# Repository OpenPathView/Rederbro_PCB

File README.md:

# Rederbro_PCB
All electronic parts related to rederbro (Open Path View, backpack).

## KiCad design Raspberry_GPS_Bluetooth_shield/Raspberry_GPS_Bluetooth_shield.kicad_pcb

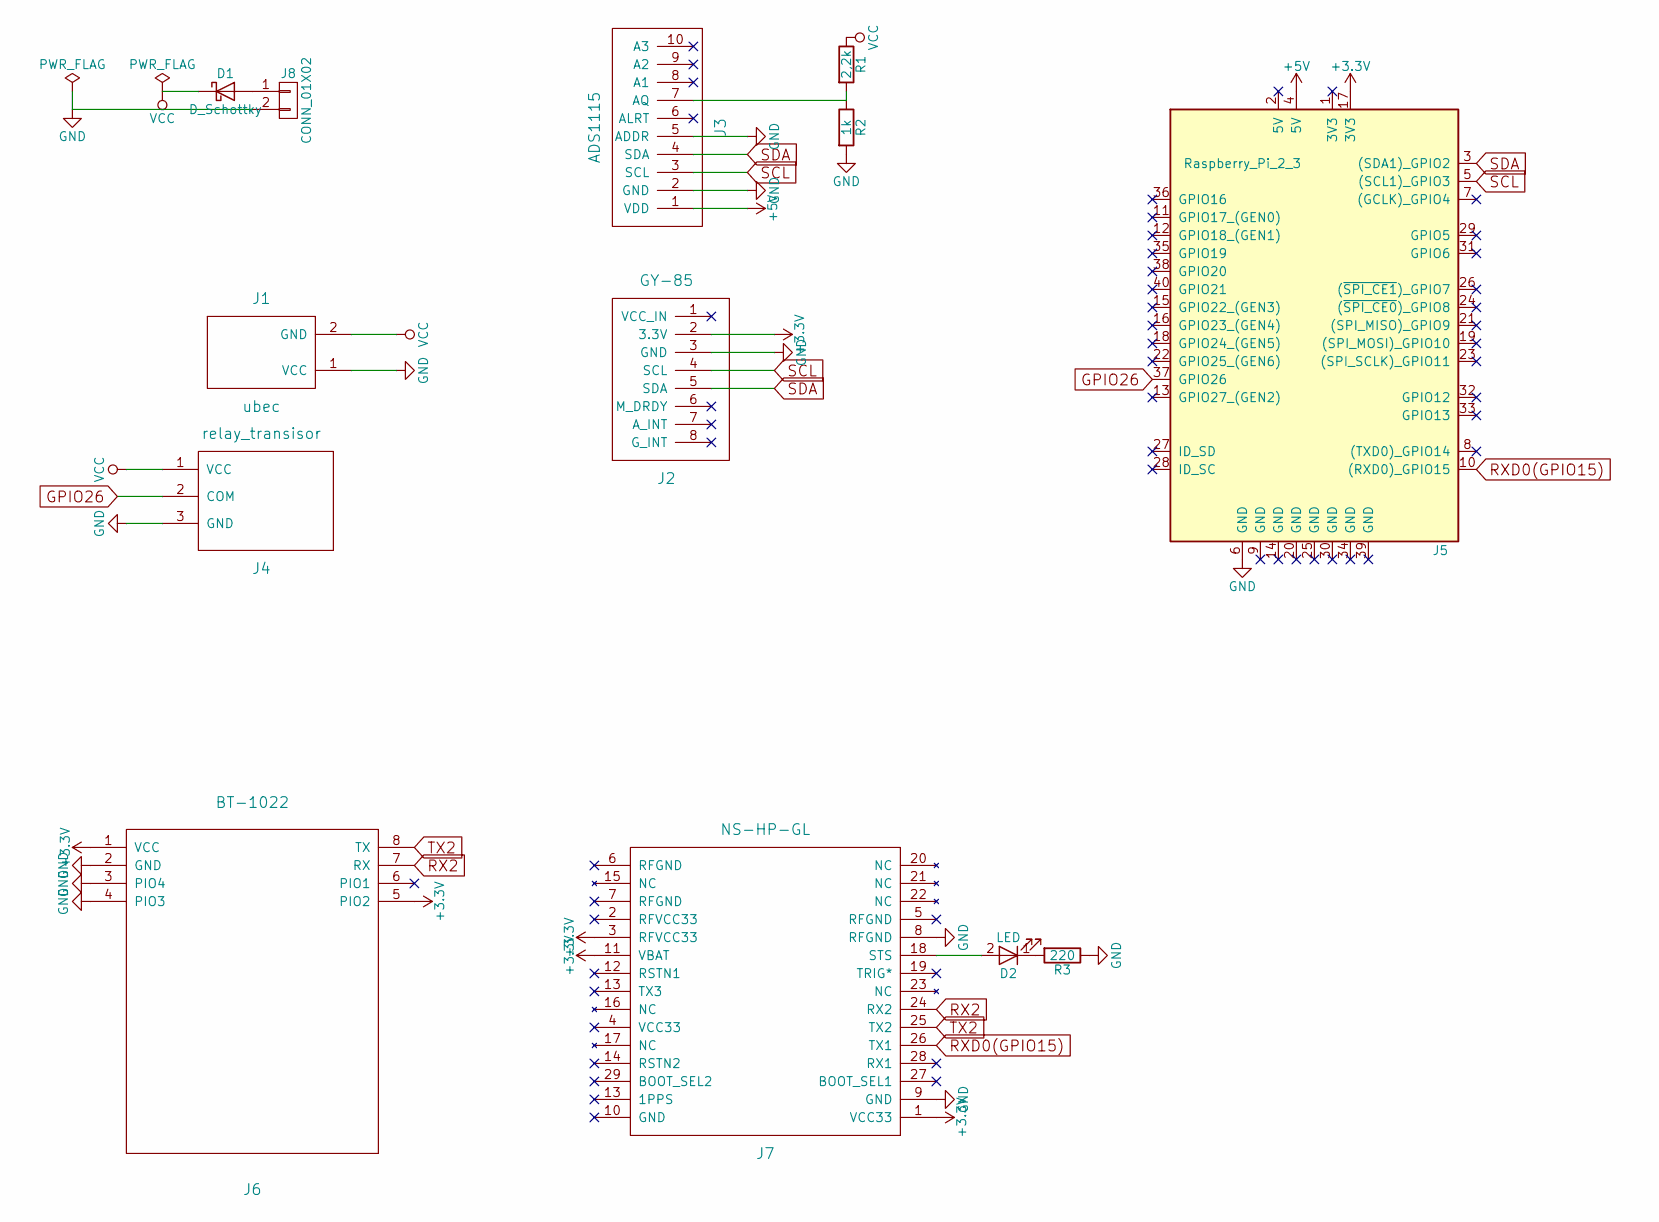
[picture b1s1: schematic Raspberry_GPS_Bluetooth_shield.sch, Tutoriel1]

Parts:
D1: D_Schottky; 1N5820
D2: LED; LED_0603
J1: ubec; PhoenixContact_MCV-G_02x3.50mm_Vertical
J2: GY-85; Pin_Header_Straight_1x08_Pitch2.54mm
J3: ADS1115; Pin_Header_Straight_1x10_Pitch2.54mm
J4: relay_transisor; PhoenixContact_MCV-G_03x5.08mm_Vertical
J5: Raspberry_Pi_2_3; Pin_Header_Straight_2x20_Pitch2.54mm
J6: BT-1022; BT_NAVSPARK
J7: NS-HP-GL
J8: CONN_01X02; PhoenixContact_MCV-G_02x3.50mm_Vertical
R1: 2,2k; R_0805_HandSoldering
R2: 1k; R_0805_HandSoldering
R3: 220; R_0805_HandSoldering

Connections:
+3V3: J2.2 (3.3V), J5.17 (3V3), J6.1 (VCC), J6.5 (PIO2), J7.1 (VCC33), J7.3 (RFVCC33), J7.11 (VBAT)
+5V: J3.1 (VDD), J5.4 (5V)
GND: J1.1 (VCC), J2.3 (GND), J3.2 (GND), J3.5 (ADDR), J4.3 (GND), J5.6 (GND), J6.2 (GND), J6.3 (PIO4), J6.4 (PIO3), J7.8 (RFGND), J7.9 (GND), J8.2, R2.2, R3.1
GPIO26: J4.2 (COM), J5.37 (GPIO26)
unnamed: D1.2 (A), J8.1
unnamed: D2.1 (K), R3.2
unnamed: D2.2 (A), J7.18 (STS)
unnamed: J3.7 (AQ), R1.2, R2.1
RX2: J6.7 (RX), J7.24 (RX2)
RXD0(GPIO15): J5.10 ((RXD0)_GPIO15), J7.26 (TX1)
SCL: J2.4 (SCL), J3.3 (SCL), J5.5 ((SCL1)_GPIO3)
SDA: J2.5 (SDA), J3.4 (SDA), J5.3 ((SDA1)_GPIO2)
TX2: J6.8 (TX), J7.25 (TX2)
VCC: D1.1 (K), J1.2 (GND), J4.1 (VCC), R1.1

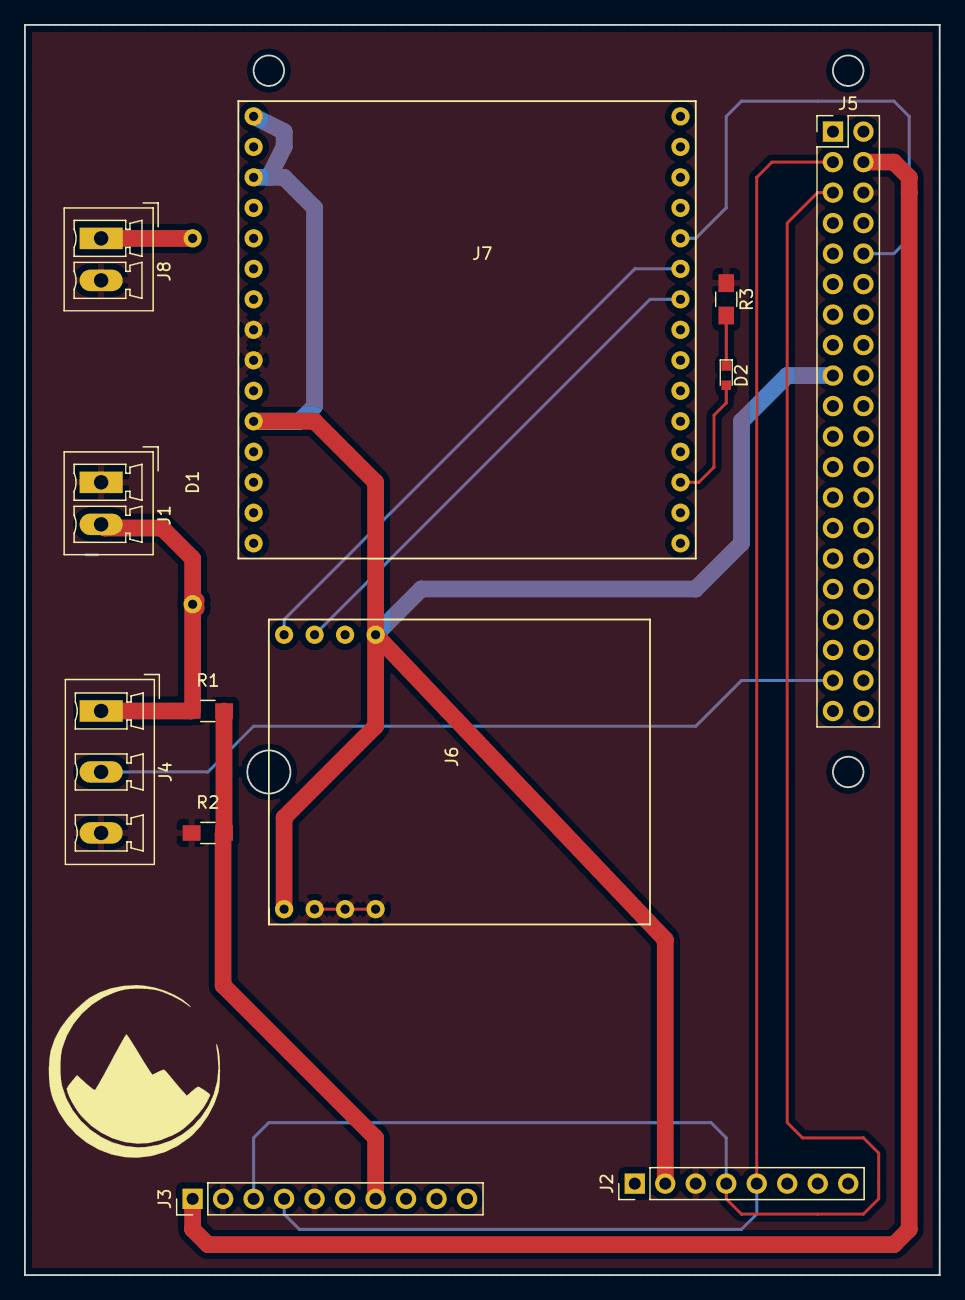
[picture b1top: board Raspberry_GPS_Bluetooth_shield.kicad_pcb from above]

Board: 2 copper layers, 76.2 x 104.1 mm, 13 parts (0 on the bottom side), 14 nets.

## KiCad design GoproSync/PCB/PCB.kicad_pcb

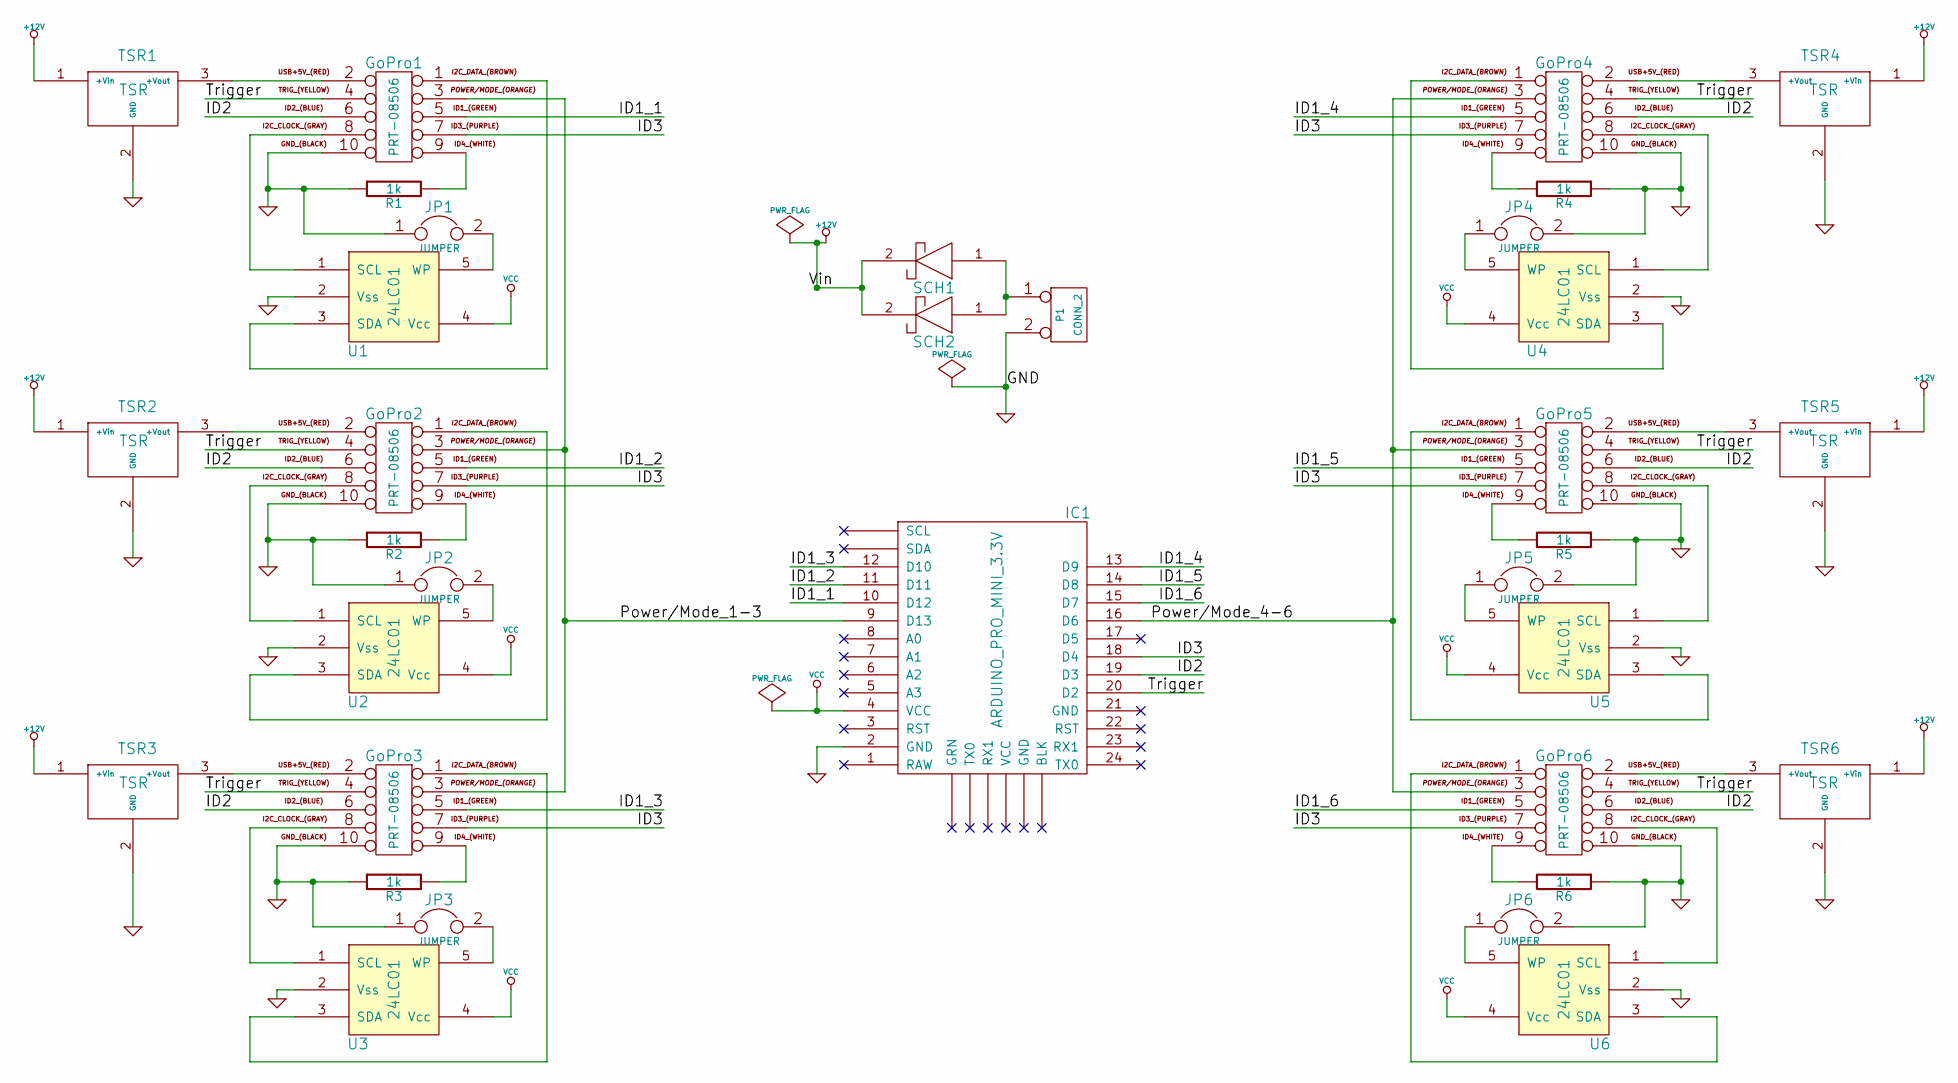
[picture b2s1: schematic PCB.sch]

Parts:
GoPro1, GoPro2, GoPro3, GoPro4, GoPro5, GoPro6: PRT-08506
IC1: ARDUINO_PRO_MINI_3.3V
JP1, JP2, JP3, JP4, JP5, JP6: JUMPER
P1: CONN_2
R1, R2, R3, R4, R5, R6: 1k
SCH1, SCH2: SCHOTTKY
TSR1, TSR2, TSR3, TSR4, TSR5, TSR6: TSR
U1, U2, U3, U4, U5, U6: 24LC01

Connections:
+12V: SCH1.2 (Cathode), SCH2.2 (Cathode), TSR1.1 (+Vin), TSR2.1 (+Vin), TSR3.1 (+Vin), TSR4.1 (+Vin), TSR5.1 (+Vin), TSR6.1 (+Vin)
/ID1_1: GoPro1.5, IC1.10 (D12)
/ID1_2: GoPro2.5, IC1.11 (D11)
/ID1_3: GoPro3.5, IC1.12 (D10)
/ID1_4: GoPro4.5, IC1.13 (D9)
/ID1_5: GoPro5.5, IC1.14 (D8)
/ID1_6: GoPro6.5, IC1.15 (D7)
/ID2: GoPro1.6, GoPro2.6, GoPro3.6, GoPro4.6, GoPro5.6, GoPro6.6, IC1.19 (D3)
/ID3: GoPro1.7, GoPro2.7, GoPro3.7, GoPro4.7, GoPro5.7, GoPro6.7, IC1.18 (D4)
/Power/Mode_1-3: GoPro1.3, GoPro2.3, GoPro3.3, IC1.9 (D13)
/Power/Mode_4-6: GoPro4.3, GoPro5.3, GoPro6.3, IC1.16 (D6)
/Trigger: GoPro1.4, GoPro2.4, GoPro3.4, GoPro4.4, GoPro5.4, GoPro6.4, IC1.20 (D2)
GND: GoPro1.10, GoPro2.10, GoPro3.10, GoPro4.10, GoPro5.10, GoPro6.10, IC1.2 (GND), JP1.1, JP2.1, JP3.1, JP4.2, JP5.2, JP6.2, P1.2 (PM), R1.1, R2.1, R3.1, R4.1, R5.1, R6.1, TSR1.2 (GND), TSR2.2 (GND), TSR3.2 (GND), TSR4.2 (GND), TSR5.2 (GND), TSR6.2 (GND), U1.2 (Vss), U2.2 (Vss), U3.2 (Vss), U4.2 (Vss), U5.2 (Vss), U6.2 (Vss)
unnamed: GoPro1.9, R1.2
unnamed: GoPro3.2, TSR3.3 (+Vout)
unnamed: GoPro3.9, R3.2
unnamed: GoPro6.9, R6.2
unnamed: GoPro6.1, U6.3 (SDA)
unnamed: GoPro6.2, TSR6.3 (+Vout)
unnamed: GoPro4.9, R4.2
unnamed: GoPro2.9, R2.2
unnamed: GoPro4.1, U4.3 (SDA)
unnamed: GoPro2.2, TSR2.3 (+Vout)
unnamed: GoPro2.8, U2.1 (SCL)
unnamed: GoPro1.2, TSR1.3 (+Vout)
unnamed: JP4.1, U4.5 (WP)
unnamed: JP1.2, U1.5 (WP)
unnamed: JP6.1, U6.5 (WP)
unnamed: GoPro6.8, U6.1 (SCL)
unnamed: JP5.1, U5.5 (WP)
unnamed: GoPro5.1, U5.3 (SDA)
unnamed: GoPro4.2, TSR4.3 (+Vout)
unnamed: GoPro4.8, U4.1 (SCL)
unnamed: GoPro5.8, U5.1 (SCL)
unnamed: GoPro5.2, TSR5.3 (+Vout)
unnamed: GoPro5.9, R5.2
unnamed: JP3.2, U3.5 (WP)
unnamed: JP2.2, U2.5 (WP)
unnamed: GoPro1.1, U1.3 (SDA)
unnamed: GoPro1.8, U1.1 (SCL)
unnamed: GoPro2.1, U2.3 (SDA)
unnamed: GoPro3.8, U3.1 (SCL)
unnamed: GoPro3.1, U3.3 (SDA)
unnamed: P1.1, SCH1.1 (Anode), SCH2.1 (Anode)
VCC: IC1.4 (VCC), U1.4 (Vcc), U2.4 (Vcc), U3.4 (Vcc), U4.4 (Vcc), U5.4 (Vcc), U6.4 (Vcc)

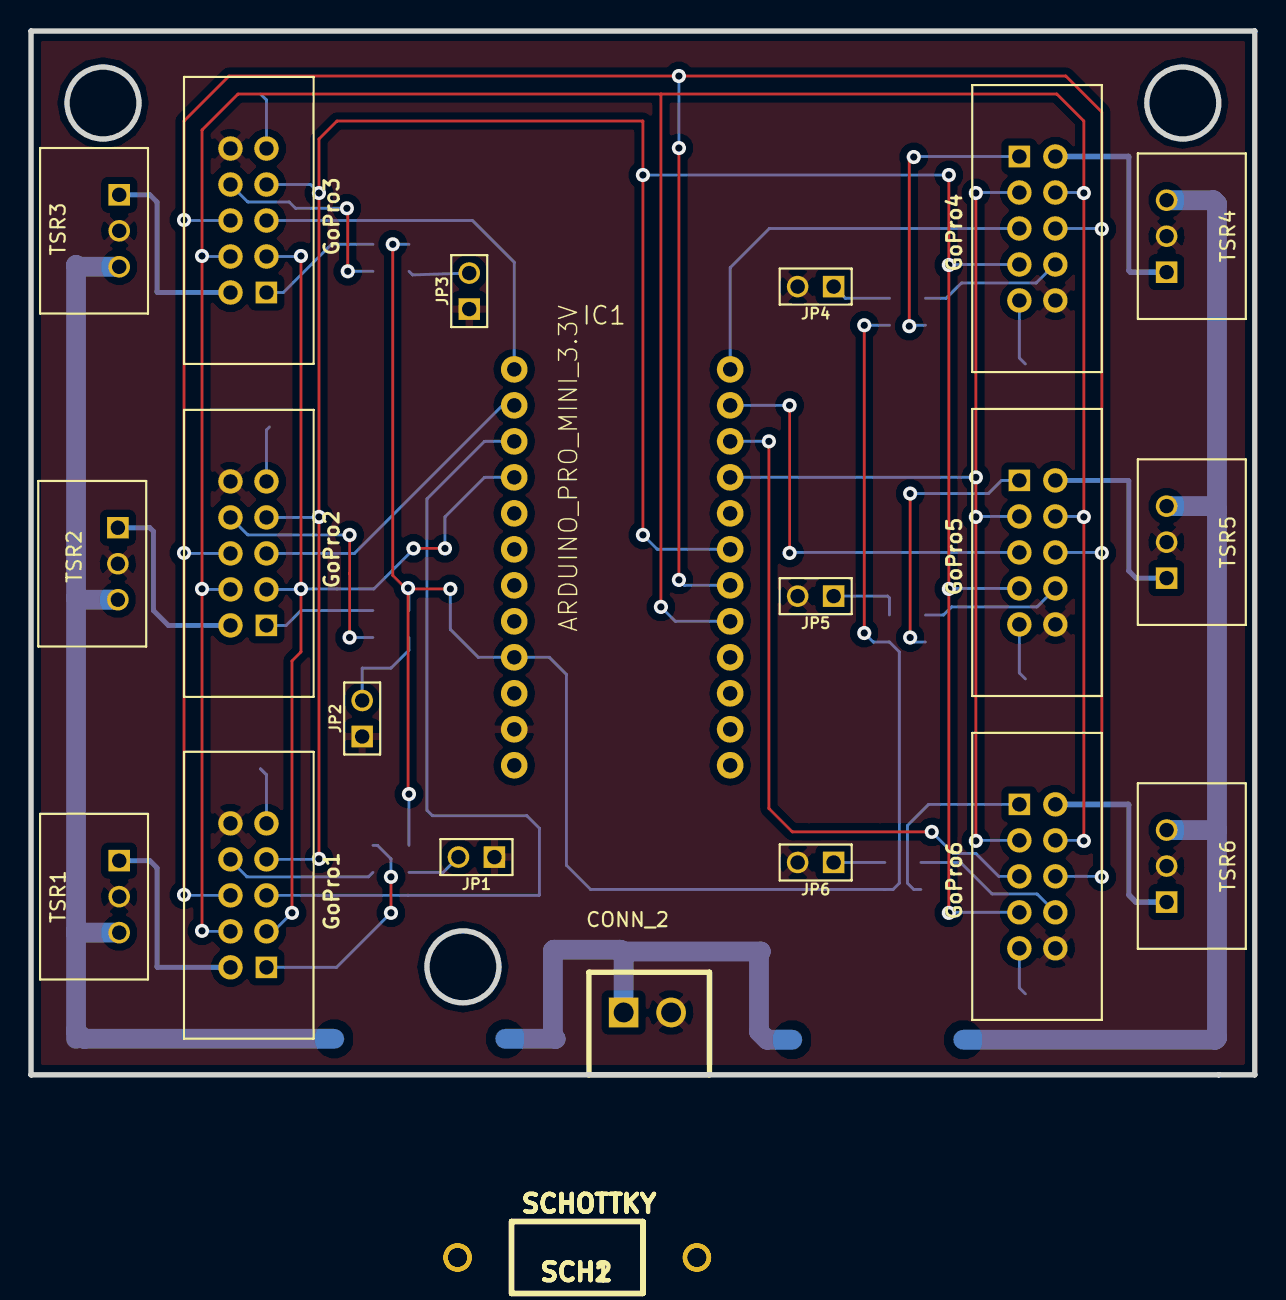
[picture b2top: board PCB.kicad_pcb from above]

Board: 2 copper layers, 86.4 x 73.7 mm, 34 parts (0 on the bottom side), 45 nets.

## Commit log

2017-05-24 PCB GoPro Sync
2017-07-03 Add PCB for Raspberry shield
